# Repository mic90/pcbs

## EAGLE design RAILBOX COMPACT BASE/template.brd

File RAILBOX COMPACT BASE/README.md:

This is the base board for ITALTRONICS Railbox Compact enclosures (https://eng.italtronic.com/products/railbox_compact_vertical_en/)

It has 8 x 5.08mm screw terminals and pinout prepared for integrated bus system

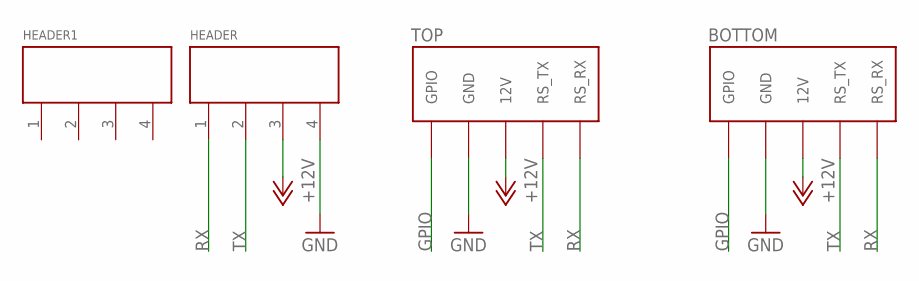
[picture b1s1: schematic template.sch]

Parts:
BOTTOM: STEROWNIK-PINY_5PIN_BOTTOM
HEADER, HEADER1: TBMP5104RO-KF
TOP: STEROWNIK-PINY_5PIN

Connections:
+12V: BOTTOM.12 (12V), HEADER.3, TOP.12V
GND: BOTTOM.GND, HEADER.4, TOP.GND
GPIO: BOTTOM.GPIO1 (GPIO), TOP.GPIO1 (GPIO)
RX: BOTTOM.RS_RX, HEADER.1, TOP.RS_RX
TX: BOTTOM.RS_TX, HEADER.2, TOP.RS_TX

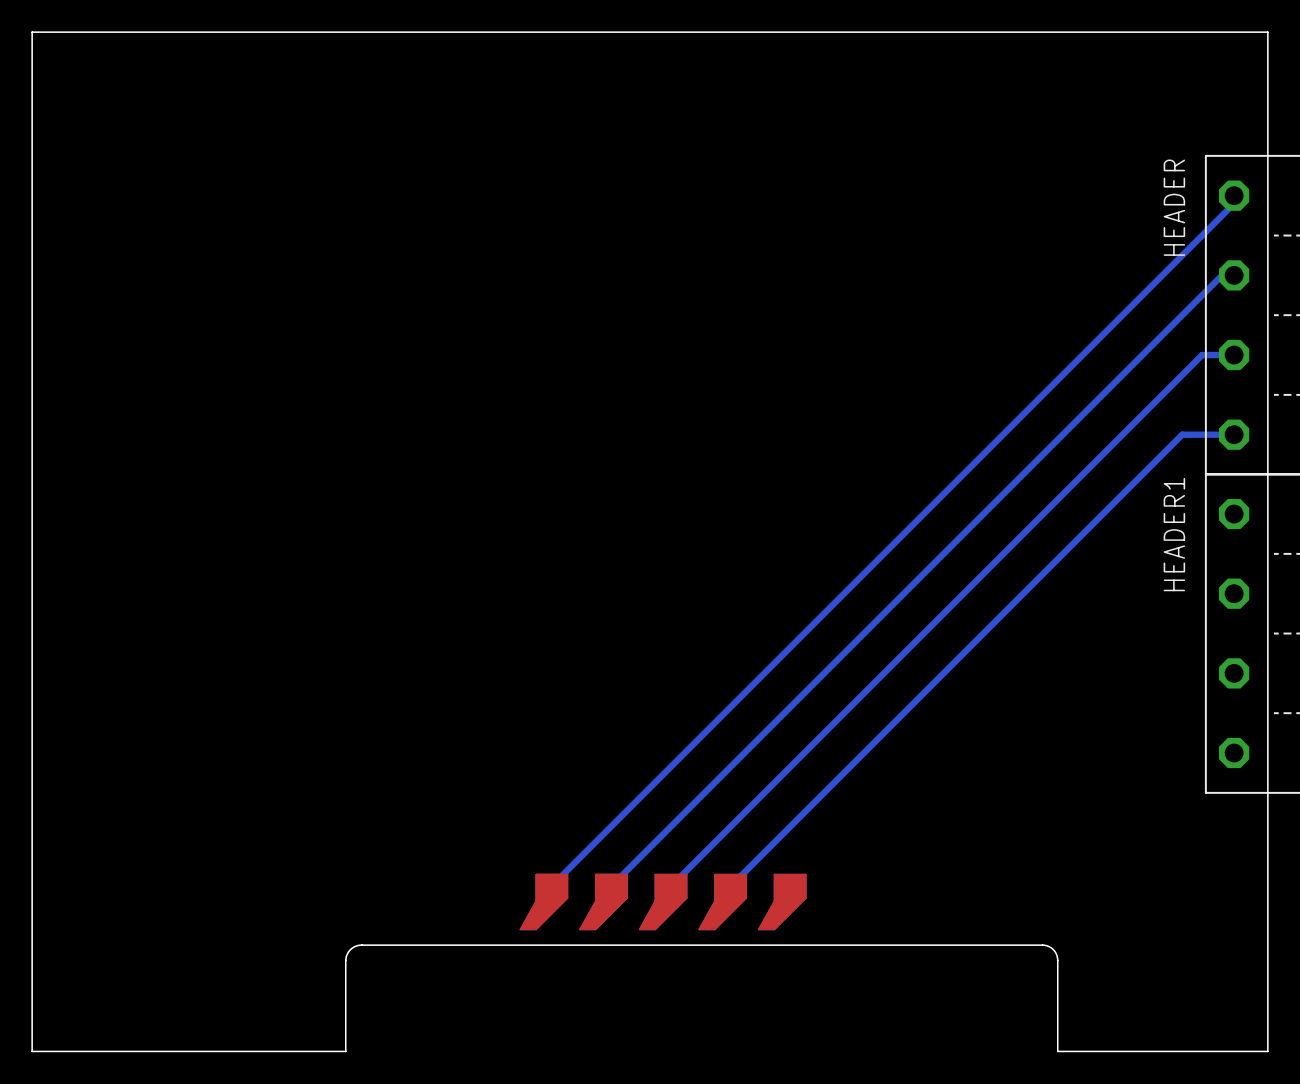
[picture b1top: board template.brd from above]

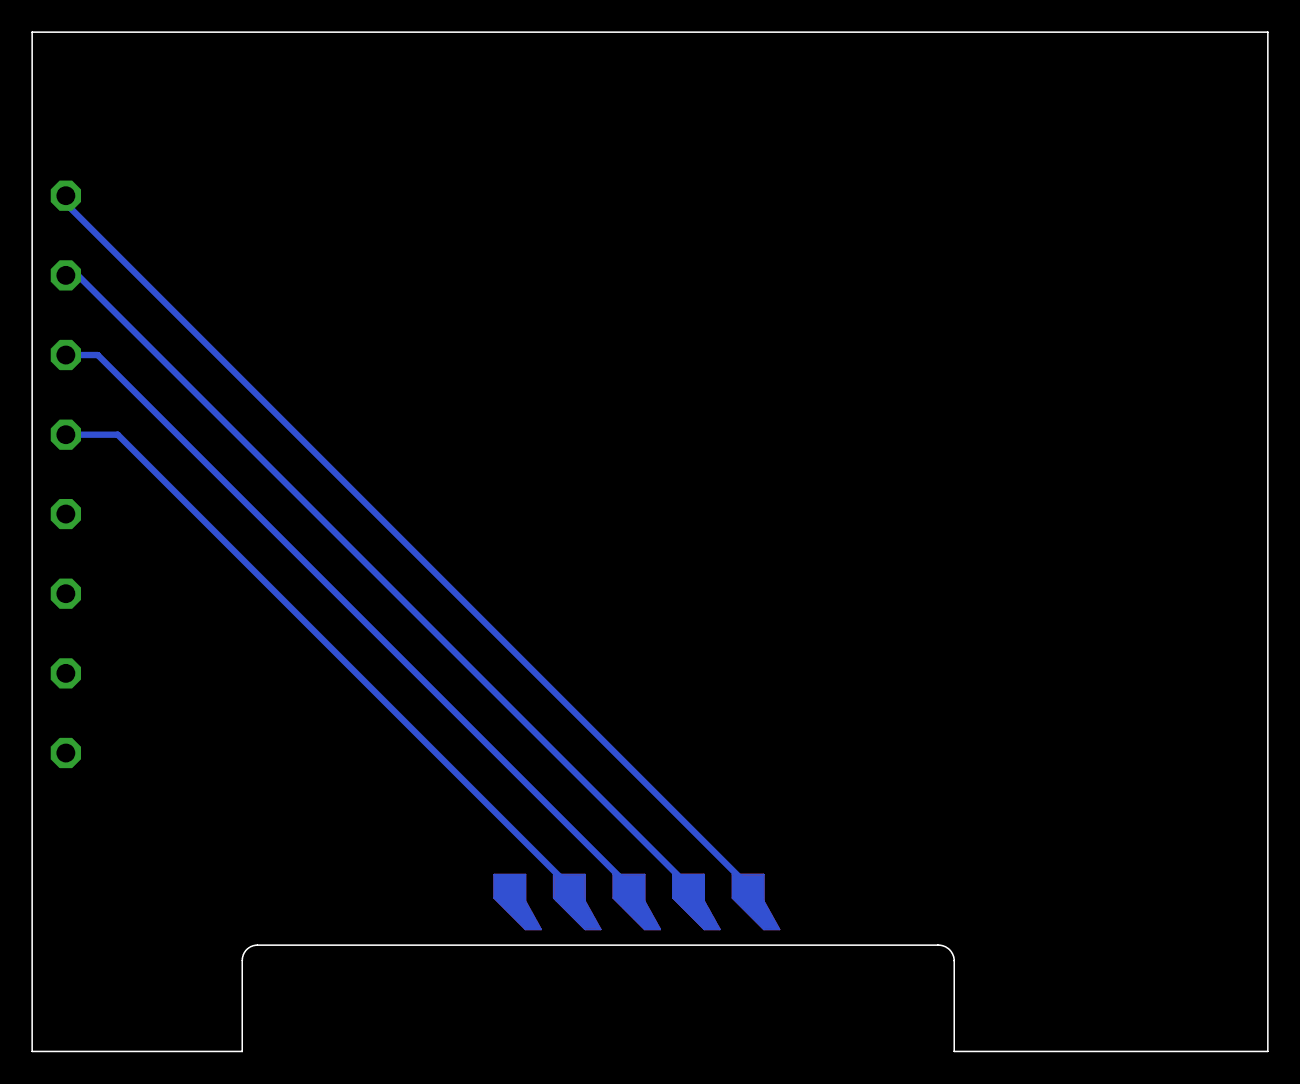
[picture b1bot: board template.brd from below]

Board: 2 copper layers, 78.8 x 65.0 mm, 4 parts (2 on the bottom side), 5 nets.

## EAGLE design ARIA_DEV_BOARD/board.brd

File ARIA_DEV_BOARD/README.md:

This is simple development board for ARIAG25 SoC module from acmesystems (https://www.acmesystems.it/aria)

The board is equipped with all basic stuff needed to start development on this platform:
* 1x Ethernet port
* 1x USB Host 
* Debug port
* WiFi module connected to USB pins
* RS485 transciever
* Voltage converters so it can be powered with 12V DC input

PCB View:

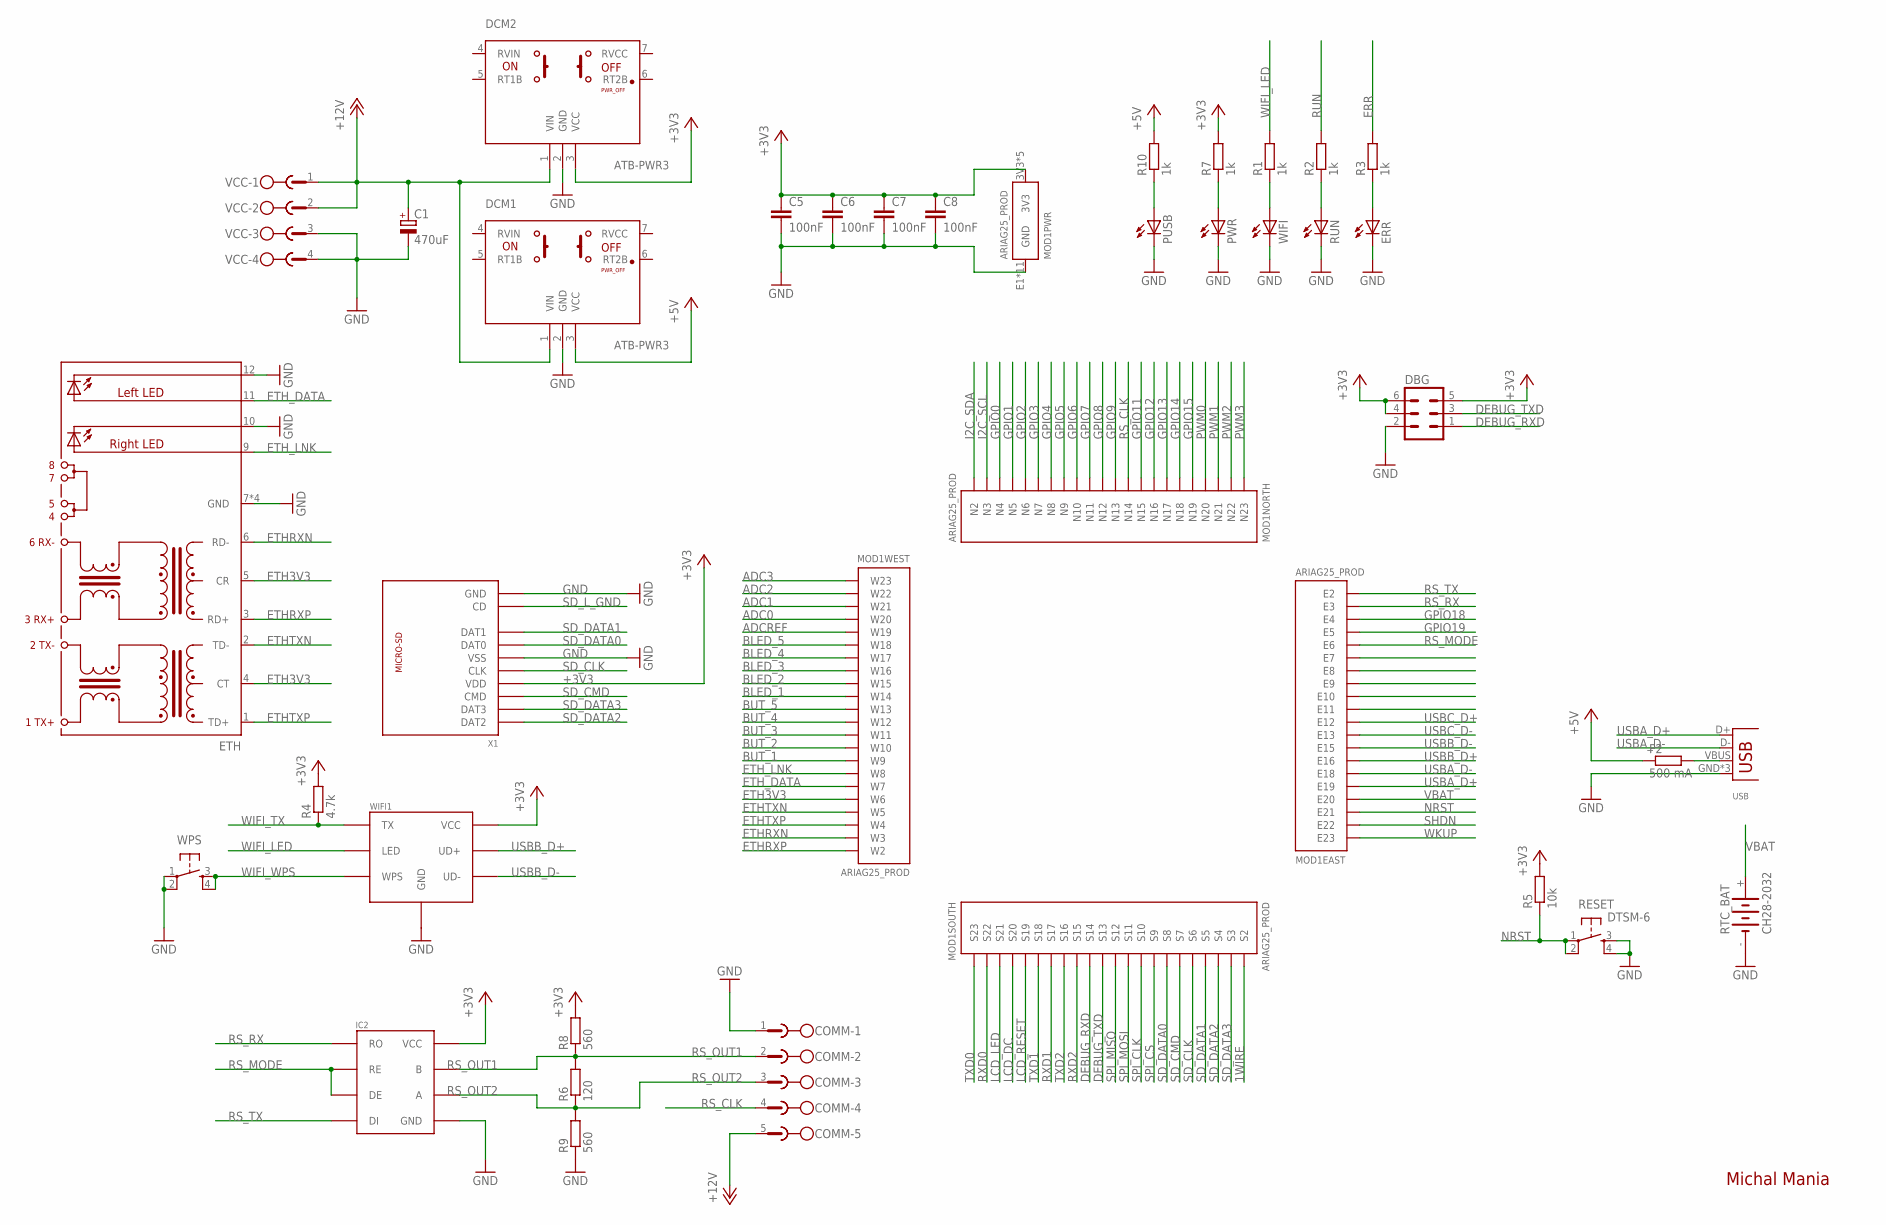
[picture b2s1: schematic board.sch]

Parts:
C1: 470uF; PANASONIC_G
C5, C6, C7, C8: 100nF; C0805
COMM: MSTBV5
DBG: MA03-2
DCM1, DCM2: ATB-PWR3
ERR: LEDSML0805; SML0805
ETH: J21388; J1_3_TOP
F2: 500 mA; R0805
IC2: MAX3485; SO-8
MOD1: ARIAG25_PROD; G25_D
PUSB: LEDSML0805; SML0805
PWR: LEDSML0805; SML0805
R1, R2, R3, R7, R10: 1k; R0805
R4: 4.7k; R0805
R5: 10k; R0805
R6: 120; R0805
R8, R9: 560; R0805
RESET: DTSM-6
RTC_BAT: CH28-2032
RUN: LEDSML0805; SML0805
USB: USBA-P; USB-A-P
VCC: MSTBV4
WIFI: LEDSML0805; SML0805
WIFI1: WIFI-2-OEM; WIFI
WPS: DTSM-6
X1: MICRO-SD; 112I-TDAR-R

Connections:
1WIRE: MOD1.S2
+3V3: C5.1, C6.1, C7.1, C8.1, DBG.4, DBG.5, DBG.6, DCM2.3 (VCC), IC2.VCC, MOD1.3V3, MOD1.E24 (3V3), MOD1.N1 (3V3), MOD1.S1 (3V3), MOD1.W24 (3V3), R4.2, R5.2, R7.2, R8.2, WIFI1.VCC, X1.4 (VDD)
+5V: DCM1.3 (VCC), F2.1, R10.2
+12V: C1.+, COMM.5, DCM1.1 (VIN), DCM2.1 (VIN), VCC.1, VCC.2
ADC0: MOD1.W20
ADC1: MOD1.W21
ADC2: MOD1.W22
ADC3: MOD1.W23
ADCREF: MOD1.W19
BLED_1: MOD1.W14
BLED_2: MOD1.W15
BLED_3: MOD1.W16
BLED_4: MOD1.W17
BLED_5: MOD1.W18
BUT_1: MOD1.W9
BUT_2: MOD1.W10
BUT_3: MOD1.W11
BUT_4: MOD1.W12
BUT_5: MOD1.W13
DEBUG_RXD: DBG.1, MOD1.S14
DEBUG_TXD: DBG.3, MOD1.S13
ERR: R3.2
ETH3V3: ETH.4 (CT), ETH.5 (CR), MOD1.W6
ETHRXN: ETH.6 (RD-), MOD1.W3
ETHRXP: ETH.3 (RD+), MOD1.W2
ETHTXN: ETH.2 (TD-), MOD1.W5
ETHTXP: ETH.1 (TD+), MOD1.W4
ETH_DATA: ETH.11 (L+), MOD1.W7
ETH_LNK: ETH.9 (R+), MOD1.W8
GND: C1.-, C5.2, C6.2, C7.2, C8.2, COMM.1, DBG.2, DCM1.2 (GND), DCM2.2 (GND), ERR.C, ETH.7 (GND), ETH.8 (GND), ETH.10 (R-), ETH.12 (L-), ETH.M1 (GND), ETH.M2 (GND), IC2.GND, MOD1.E1 (GND), MOD1.E14 (GND), MOD1.E17 (GND), MOD1.GND@1 (GND), MOD1.GND@2 (GND), MOD1.GND@3 (GND), MOD1.GND@4 (GND), MOD1.GND@5 (GND), MOD1.N24 (GND), MOD1.S24 (GND), MOD1.W1 (GND), PUSB.C, PWR.C, R9.1, RESET.3, RESET.4, RTC_BAT.-, RUN.C, USB.GND, USB.P$5 (GND), USB.P$6 (GND), VCC.3, VCC.4, WIFI.C, WIFI1.GND, WPS.1, WPS.2, X1.6 (VSS), X1.GND_A (GND), X1.GND_B (GND), X1.GND_C (GND)
GPIO0: MOD1.N4
GPIO1: MOD1.N5
GPIO2: MOD1.N6
GPIO3: MOD1.N7
GPIO4: MOD1.N8
GPIO5: MOD1.N9
GPIO6: MOD1.N10
GPIO7: MOD1.N11
GPIO8: MOD1.N12
GPIO9: MOD1.N13
GPIO11: MOD1.N15
GPIO12: MOD1.N16
GPIO13: MOD1.N17
GPIO14: MOD1.N18
GPIO15: MOD1.N19
GPIO18: MOD1.E4
GPIO19: MOD1.E5
I2C_SCL: MOD1.N3
I2C_SDA: MOD1.N2
LCD_DC: MOD1.S20
LCD_LED: MOD1.S21
LCD_RESET: MOD1.S19
unnamed: R1.1, WIFI.A
unnamed: F2.2, USB.VBUS
unnamed: R2.1, RUN.A
unnamed: ERR.A, R3.1
unnamed: PWR.A, R7.1
unnamed: PUSB.A, R10.1
NRST: MOD1.E21, R5.1, RESET.1, RESET.2
PWM0: MOD1.N20
PWM1: MOD1.N21
PWM2: MOD1.N22
PWM3: MOD1.N23
RS_CLK: COMM.4, MOD1.N14
RS_MODE: IC2.DE, IC2.RE, MOD1.E6
RS_OUT1: COMM.2, IC2.B, R6.2, R8.1
RS_OUT2: COMM.3, IC2.A, R6.1, R9.2
RS_RX: IC2.RO, MOD1.E3
RS_TX: IC2.DI, MOD1.E2
RUN: R2.2
RXD0: MOD1.S22
RXD1: MOD1.S17
RXD2: MOD1.S15
SD_CLK: MOD1.S6, X1.5 (CLK)
SD_CMD: MOD1.S7, X1.3 (CMD)
SD_DATA0: MOD1.S8, X1.7 (DAT0)
SD_DATA1: MOD1.S5, X1.8 (DAT1)
SD_DATA2: MOD1.S4, X1.1 (DAT2)
SD_DATA3: MOD1.S3, X1.2 (DAT3)
SD_L_GND: X1.CD
SHDN: MOD1.E22
SPI_CLK: MOD1.S10
SPI_CS: MOD1.S9
SPI_MISO: MOD1.S12
SPI_MOSI: MOD1.S11
TXD0: MOD1.S23
TXD1: MOD1.S18
TXD2: MOD1.S16
USBA_D+: MOD1.E19, USB.D+
USBA_D-: MOD1.E18, USB.D-
USBB_D+: MOD1.E16, WIFI1.UD+
USBB_D-: MOD1.E15, WIFI1.UD-
USBC_D+: MOD1.E12
USBC_D-: MOD1.E13
VBAT: MOD1.E20, RTC_BAT.+
WIFI_LED: R1.2, WIFI1.LED
WIFI_TX: R4.1, WIFI1.TX
WIFI_WPS: WIFI1.WPS, WPS.3, WPS.4
WKUP: MOD1.E23

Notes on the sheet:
Michal Mania

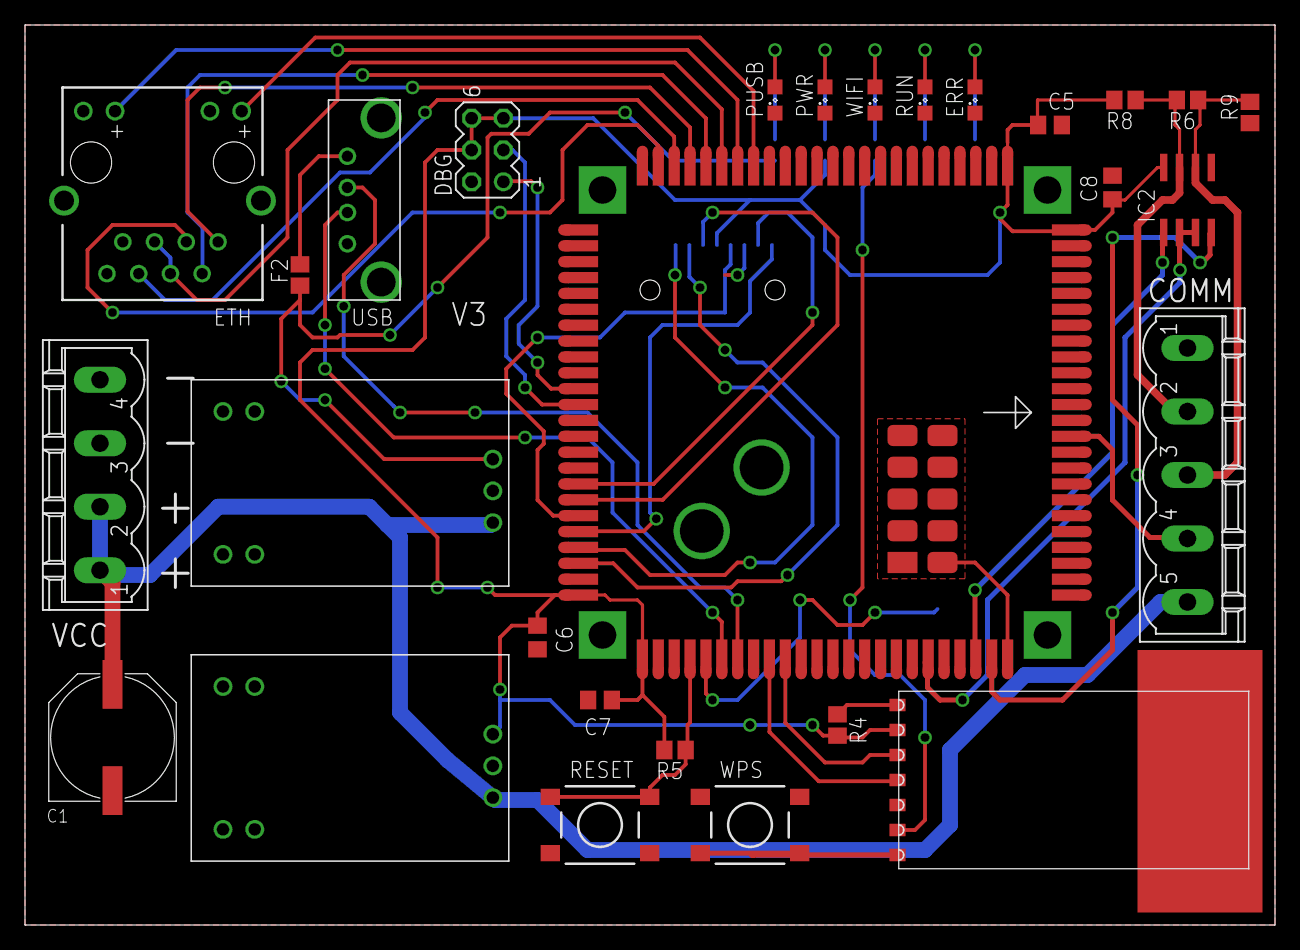
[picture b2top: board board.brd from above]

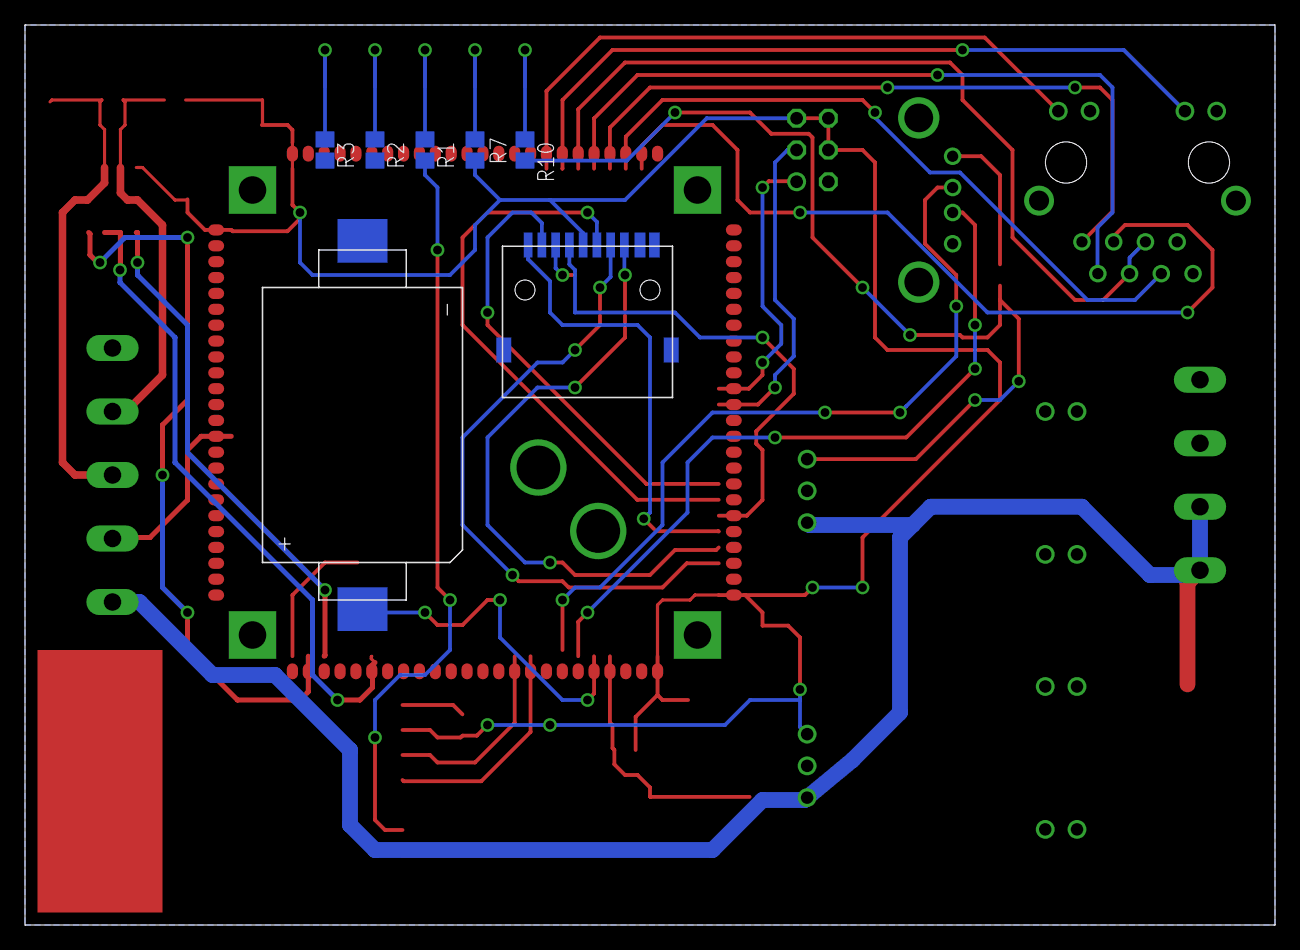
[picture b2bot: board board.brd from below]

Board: 2 copper layers, 100.0 x 72.0 mm, 35 parts (7 on the bottom side), 40 nets.

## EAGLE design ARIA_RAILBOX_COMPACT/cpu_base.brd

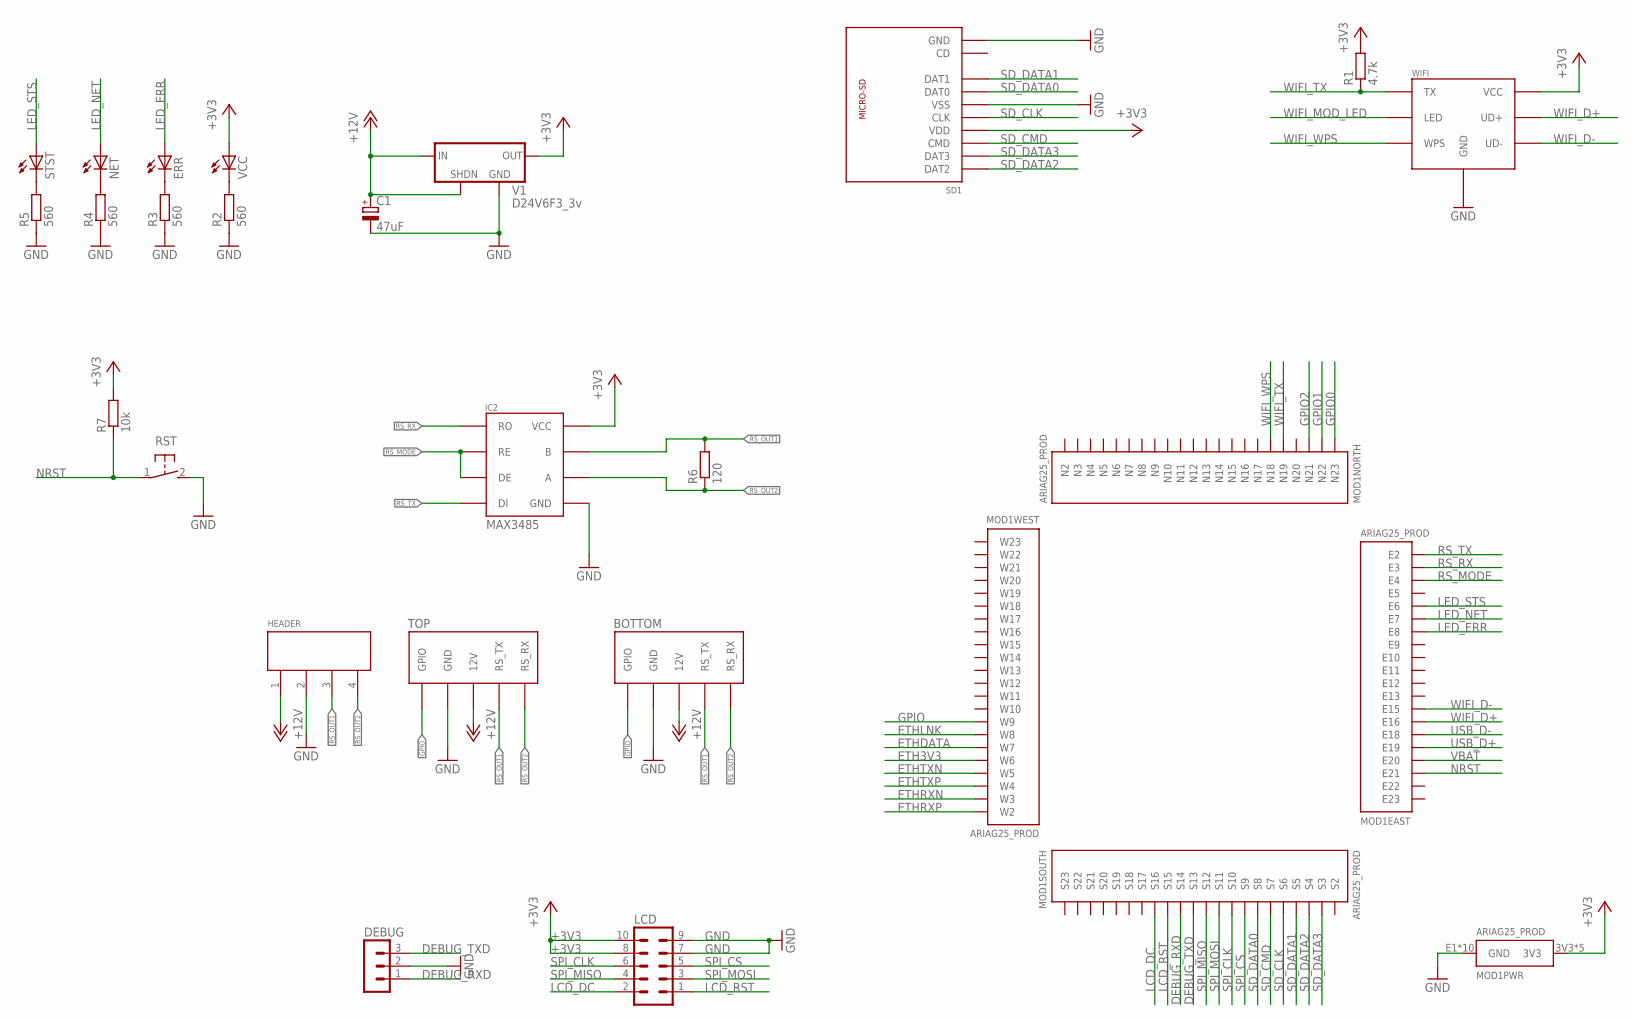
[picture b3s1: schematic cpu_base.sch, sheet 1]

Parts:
BOTTOM: STEROWNIK-PINY_5PIN_BOTTOM
C1: 47uF; 153CLV-0810
DEBUG: MA03-1
ERR: LEDCHIPLED_0805; CHIPLED_0805
HEADER: TBMP5104RO-KF
IC2: MAX3485; SO-8
LCD: MA05-2
MOD1: ARIAG25_PROD; G25_D
NET: LEDCHIPLED_0805; CHIPLED_0805
R1: 4.7k; R0805
R2, R3, R4, R5: 560; R0805
R6: 120; R0805
R7: 10k; R0805
RST: 31-XX; B3F-31XX
SD1: MICRO-SD; 112I-TDAR-R
STST: LEDCHIPLED_0805; CHIPLED_0805
TOP: STEROWNIK-PINY_5PIN
V1: D24V6F3_3v; D24V6F5_5V
VCC: LEDCHIPLED_0805; CHIPLED_0805
WIFI: WIFI-2-OEM; WIFI

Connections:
+3V3: IC2.VCC, LCD.8, LCD.10, MOD1.3V3, MOD1.E24 (3V3), MOD1.N1 (3V3), MOD1.S1 (3V3), MOD1.W24 (3V3), R1.2, R7.2, SD1.4 (VDD), V1.VOUT (OUT), VCC.A, WIFI.VCC
+12V: BOTTOM.12 (12V), C1.+, HEADER.1, TOP.12V, V1.SHDN, V1.VIN (IN)
DEBUG_RXD: DEBUG.1, MOD1.S14
DEBUG_TXD: DEBUG.3, MOD1.S13
ETH3V3: MOD1.W6
ETHDATA: MOD1.W7
ETHLNK: MOD1.W8
ETHRXN: MOD1.W3
ETHRXP: MOD1.W2
ETHTXN: MOD1.W5
ETHTXP: MOD1.W4
GND: BOTTOM.GND, C1.-, DEBUG.2, HEADER.2, IC2.GND, LCD.7, LCD.9, MOD1.E1 (GND), MOD1.E14 (GND), MOD1.E17 (GND), MOD1.GND@1 (GND), MOD1.GND@2 (GND), MOD1.GND@4 (GND), MOD1.GND@5 (GND), MOD1.N24 (GND), MOD1.S24 (GND), MOD1.W1 (GND), R2.1, R3.1, R4.1, R5.1, RST.2 (S), SD1.6 (VSS), SD1.GND_A (GND), SD1.GND_B (GND), SD1.GND_C (GND), TOP.GND, V1.GND, WIFI.GND
GPIO: BOTTOM.GPIO1 (GPIO), MOD1.W9, TOP.GPIO1 (GPIO)
GPIO0: MOD1.N23
GPIO1: MOD1.N22
GPIO2: MOD1.N21
LCD_DC: LCD.2, MOD1.S16
LCD_RST: LCD.1, MOD1.S15
LED_ERR: ERR.A, MOD1.E8
LED_NET: MOD1.E7, NET.A
LED_STS: MOD1.E6, STST.A
unnamed: R2.2, VCC.C
unnamed: ERR.C, R3.2
unnamed: NET.C, R4.2
unnamed: R5.2, STST.C
NRST: MOD1.E21, R7.1, RST.1
RS_MODE: IC2.DE, IC2.RE, MOD1.E4
RS_OUT1: BOTTOM.RS_TX, HEADER.3, IC2.B, R6.2, TOP.RS_TX
RS_OUT2: BOTTOM.RS_RX, HEADER.4, IC2.A, R6.1, TOP.RS_RX
RS_RX: IC2.RO, MOD1.E3
RS_TX: IC2.DI, MOD1.E2
SD_CLK: MOD1.S6, SD1.5 (CLK)
SD_CMD: MOD1.S7, SD1.3 (CMD)
SD_DATA0: MOD1.S8, SD1.7 (DAT0)
SD_DATA1: MOD1.S5, SD1.8 (DAT1)
SD_DATA2: MOD1.S4, SD1.1 (DAT2)
SD_DATA3: MOD1.S3, SD1.2 (DAT3)
SPI_CLK: LCD.6, MOD1.S10
SPI_CS: LCD.5, MOD1.S9
SPI_MISO: LCD.4, MOD1.S12
SPI_MOSI: LCD.3, MOD1.S11
USB_D+: MOD1.E19
USB_D-: MOD1.E18
VBAT: MOD1.E20
WIFI_D+: MOD1.E16, WIFI.UD+
WIFI_D-: MOD1.E15, WIFI.UD-
WIFI_MOD_LED: WIFI.LED
WIFI_TX: MOD1.N19, R1.1, WIFI.TX
WIFI_WPS: MOD1.N18, WIFI.WPS

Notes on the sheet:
MAX3485

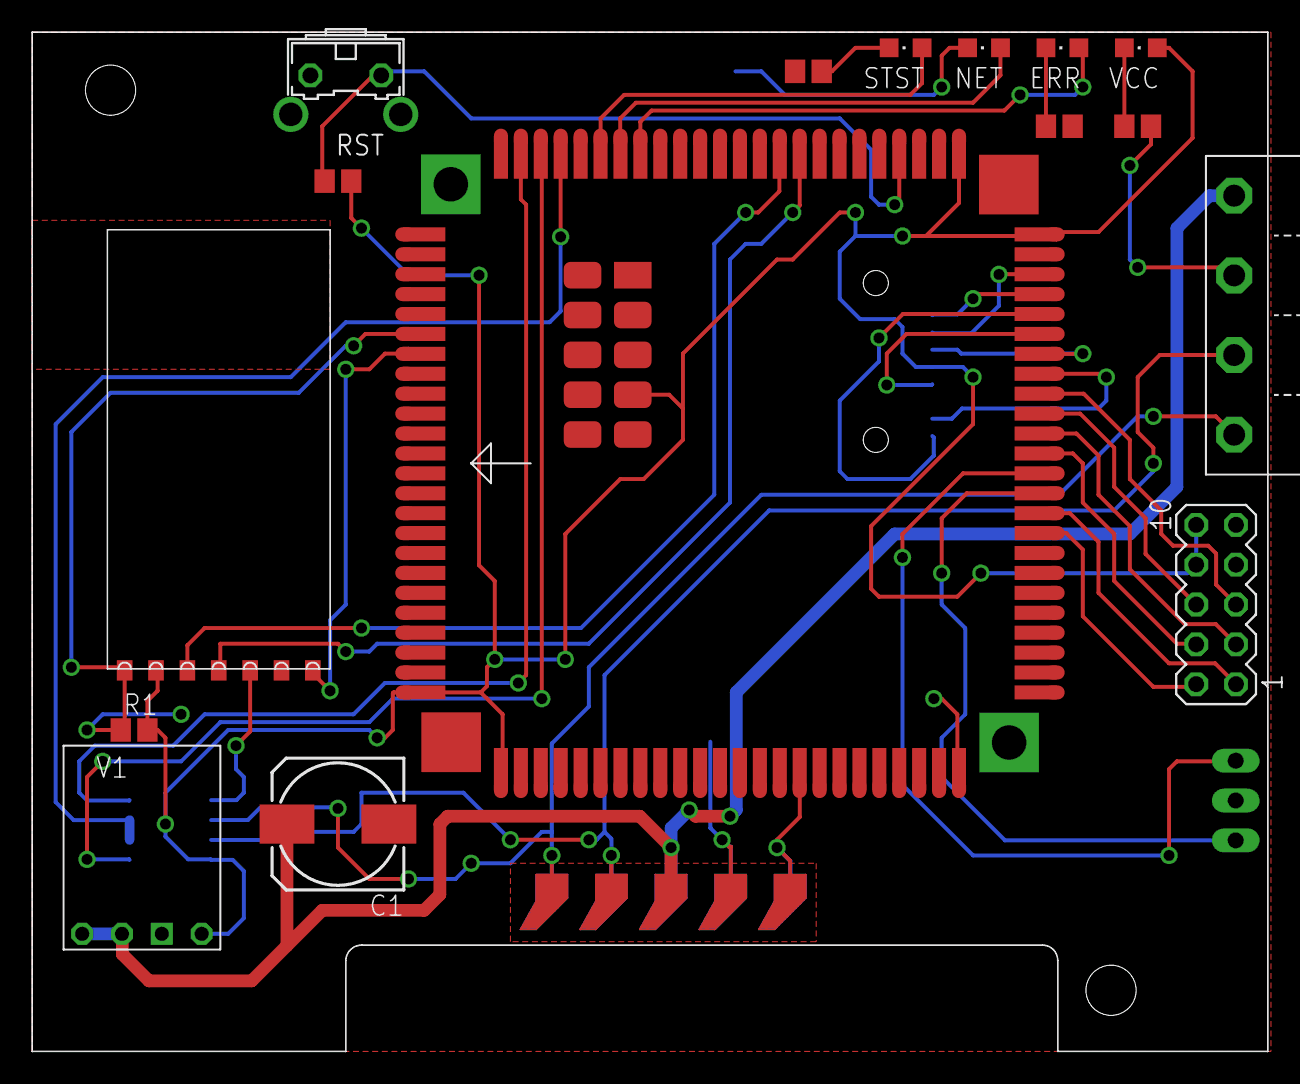
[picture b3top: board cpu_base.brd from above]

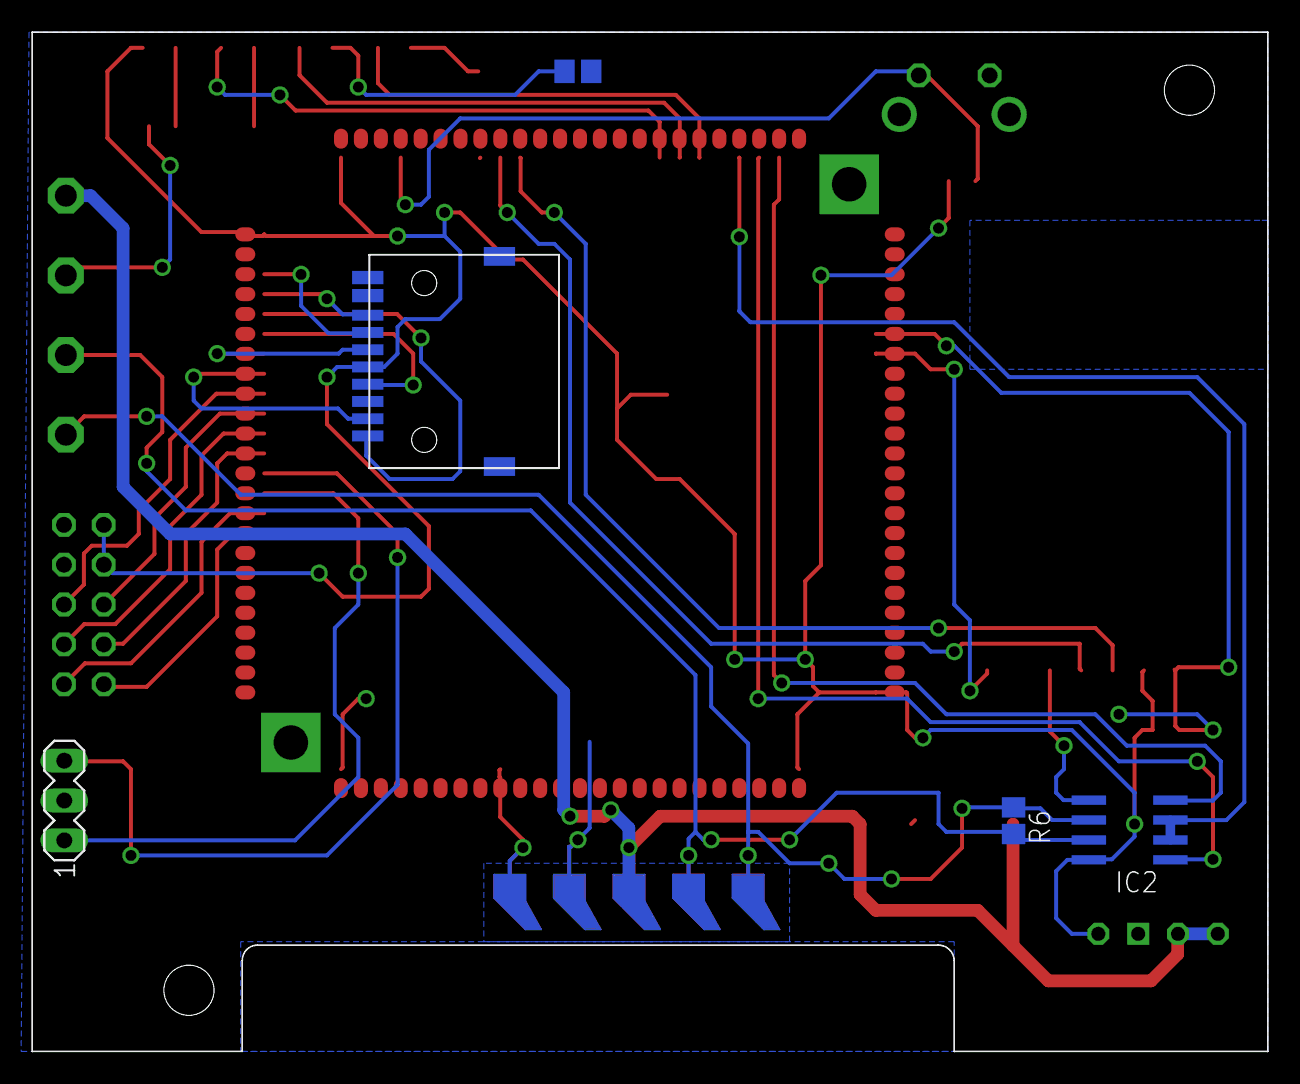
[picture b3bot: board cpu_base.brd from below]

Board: 2 copper layers, 78.8 x 65.0 mm, 23 parts (7 on the bottom side), 35 nets.

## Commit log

2018-06-05 Railbox Compact PCBS and ARIAG25 dev board
2018-06-05 ARIA dev board description
2018-06-05 Railbox compact base readme
